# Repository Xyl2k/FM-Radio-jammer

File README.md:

# FM-Radio-jammer
Board layout for http://www.circuitstoday.com/fm-radio-jammer

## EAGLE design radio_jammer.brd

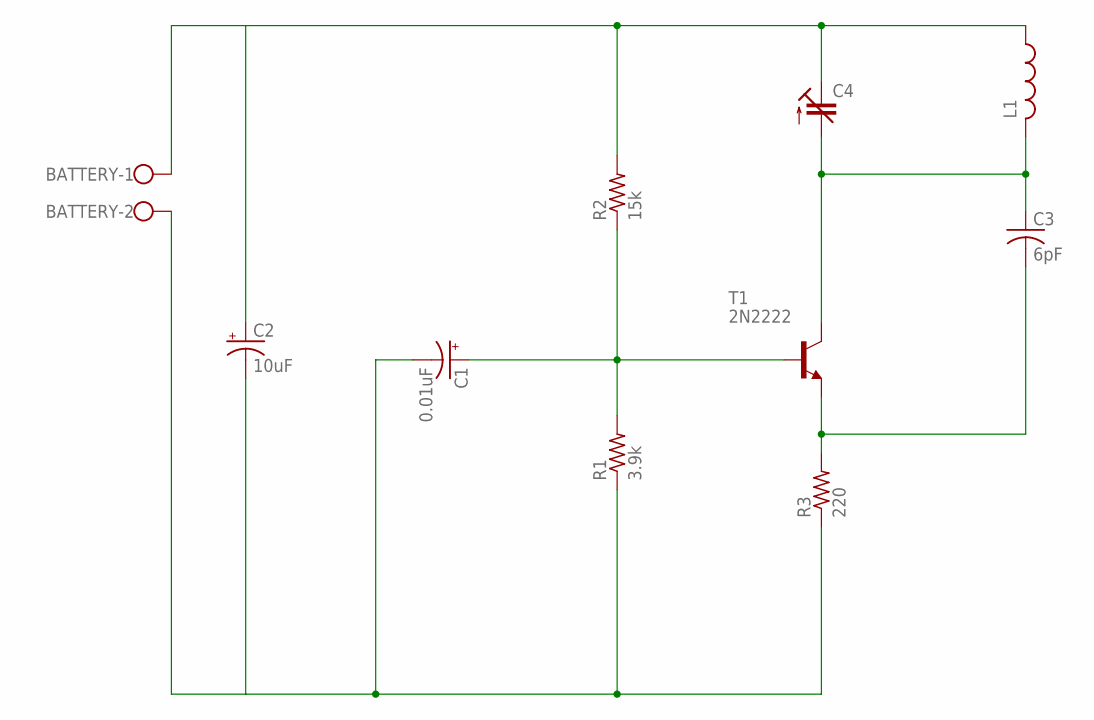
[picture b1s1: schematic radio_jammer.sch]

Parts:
BATTERY: W237-102
C1: 0.01uF; B45181A
C2: 10uF; B45181A
C3: 6pF; C025-025X050
C4: C-TRIMM3050.504; CTRIM3050.504
L1: L-US0204/7; 0204/7
R1: 3.9k; 0204/7
R2: 15k; 0204/7
R3: 220; 0204/7
T1: 2N2222; TO18

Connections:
unnamed: C1.+, R1.2, R2.1, T1.2 (B)
unnamed: BATTERY.2, C1.-, C2.-, R1.1, R3.1
unnamed: C3.2, R3.2, T1.1 (E)
unnamed: C3.1, C4.2 (A), L1.2, T1.3 (C)
unnamed: BATTERY.1, C2.+, C4.1 (E), L1.1, R2.2

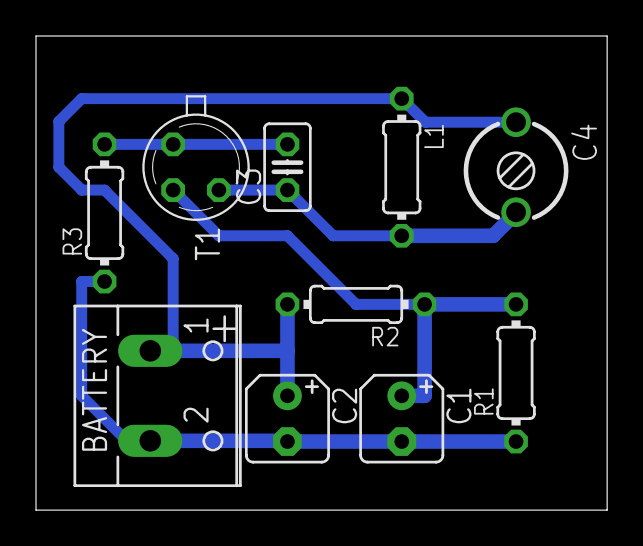
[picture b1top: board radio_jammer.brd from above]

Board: 2 copper layers, 31.7 x 26.3 mm, 10 parts (0 on the bottom side), 5 nets.

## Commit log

2015-01-07 :circus_tent: Added .gitattributes & .gitignore files
2015-01-07 1.0
    1.0
